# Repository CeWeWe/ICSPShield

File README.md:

# ICSPShield
Schematic and PCB layout for ICSP shield used with Arduino

- CWW

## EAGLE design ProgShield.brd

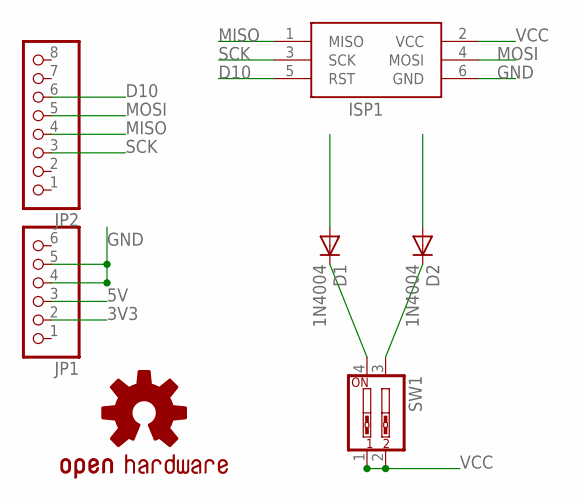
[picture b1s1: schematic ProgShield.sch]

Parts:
D1, D2: 1N4004; DO41-10
ISP1: AVRISP-6; AVRISP
JP1: PINHD-1X6CB; 1X06-CLEANBIG
JP2: PINHD-1X8CLEANBIG; 1X08-CLEANBIG
SW1: SW_DIP-2; EDG-02
U$1: OSHW-LOGOL; OSHW-LOGO-L

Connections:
3V3: D2.A, JP1.2
5V: D1.A, JP1.3
D10: ISP1.5 (RST), JP2.6
GND: ISP1.6 (GND), JP1.4, JP1.5
MISO: ISP1.1 (MISO), JP2.4
MOSI: ISP1.4 (MOSI), JP2.5
unnamed: D1.C, SW1.4
unnamed: D2.C, SW1.3
SCK: ISP1.3 (SCK), JP2.3
VCC: ISP1.2 (VCC), SW1.1, SW1.2

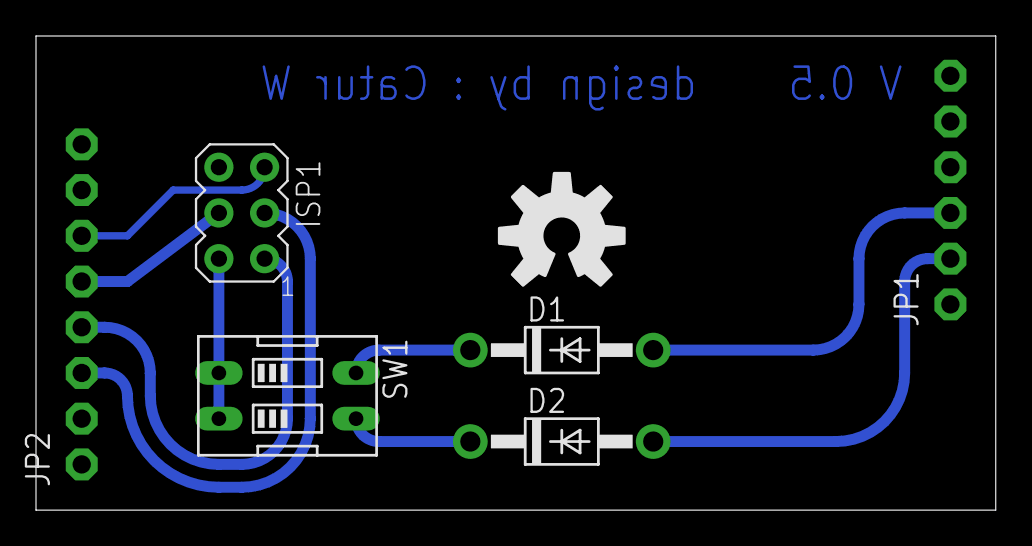
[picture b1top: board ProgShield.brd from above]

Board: 2 copper layers, 53.3 x 26.3 mm, 7 parts (0 on the bottom side), 10 nets.

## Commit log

2015-04-30 Version 0.2

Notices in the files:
parts and their libraries:
SparkFun-Aesthetics: Licensing: CC v3.0 Share-Alike You are welcome to use this library for commercial purposes.
